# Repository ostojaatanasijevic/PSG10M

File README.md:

# PSG10M

PSG10M is a simple 10 MHz signal generator.

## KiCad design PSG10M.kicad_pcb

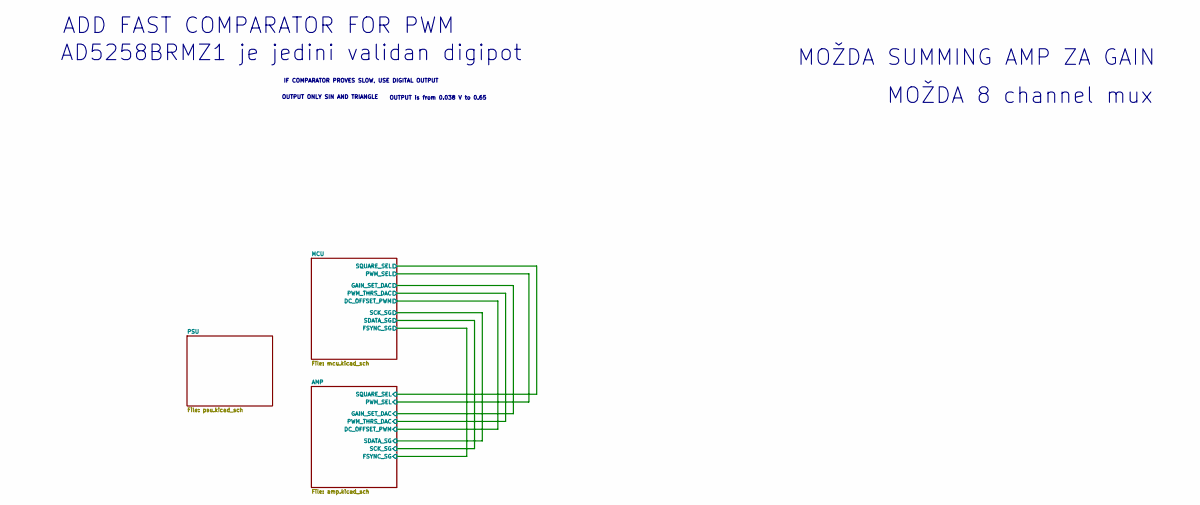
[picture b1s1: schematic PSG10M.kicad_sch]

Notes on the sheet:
OUTPUT is from 0.038 V to 0.65
IF COMPARATOR PROVES SLOW, USE DIGITAL OUTPUT
ADD FAST COMPARATOR FOR PWM
MOŽDA 8 channel mux
OUTPUT ONLY SIN AND TRIANGLE
AD5258BRMZ1 je jedini validan digipot
MOŽDA SUMMING AMP ZA GAIN

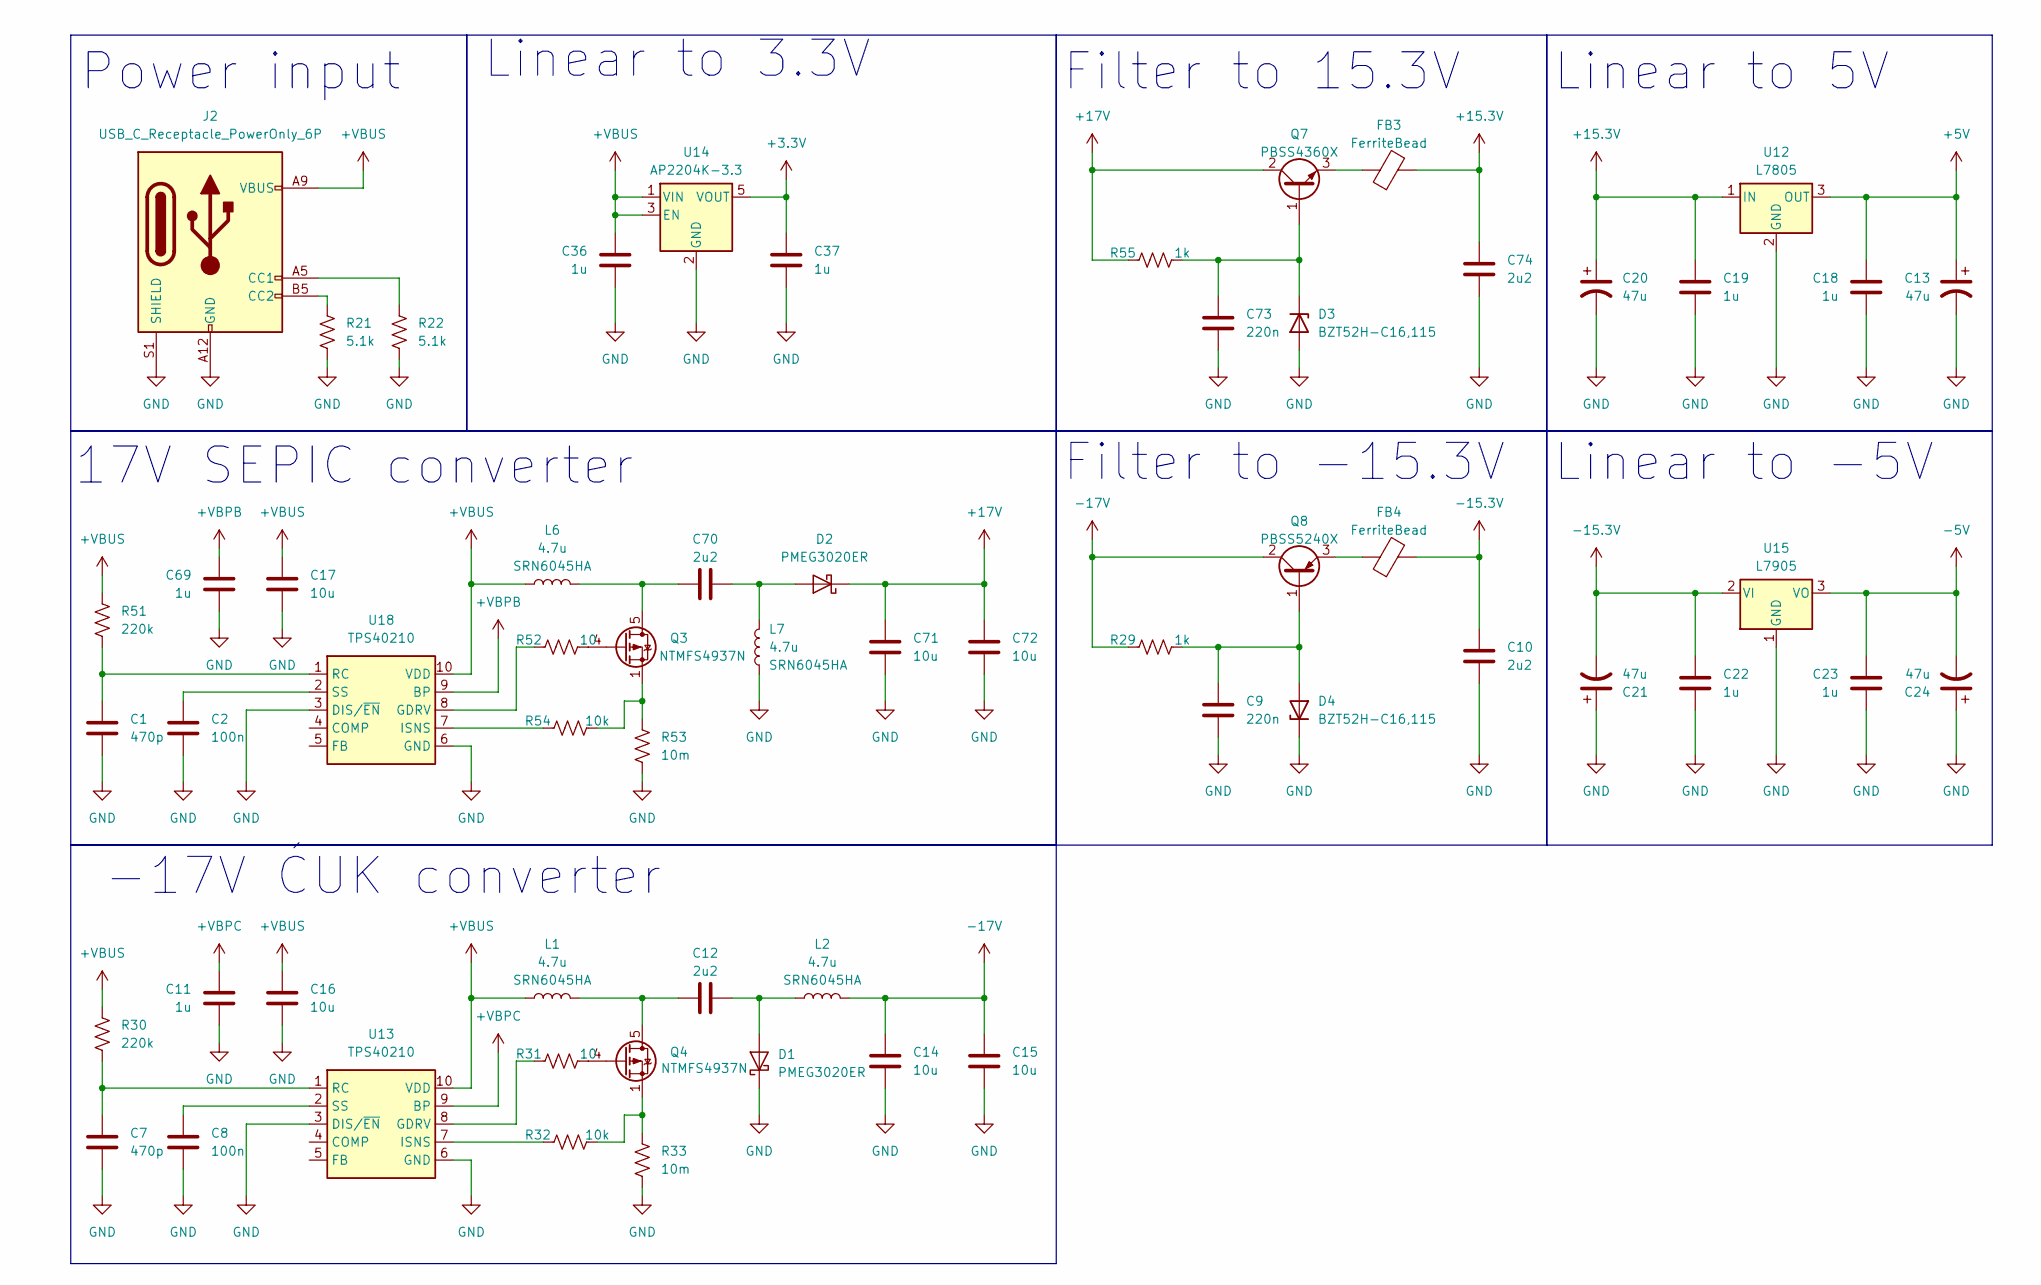
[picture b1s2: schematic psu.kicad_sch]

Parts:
C1, C7: 470p; R_0603_1608Metric_Pad0.98x0.95mm_HandSolder
C2, C8: 100n; R_0603_1608Metric_Pad0.98x0.95mm_HandSolder
C9, C73: 220n; R_0603_1608Metric_Pad0.98x0.95mm_HandSolder
C10, C12, C70, C74: 2u2; R_1206_3216Metric_Pad1.30x1.75mm_HandSolder
C11, C18, C19, C22, C23, C36, C37, C69: 1u; R_0603_1608Metric_Pad0.98x0.95mm_HandSolder
C13, C20, C21, C24: 47u; CP_Radial_D5.0mm_P2.00mm
C14, C15, C16, C17, C71, C72: 10u; R_1206_3216Metric
D1, D2: PMEG3020ER; D_SOD-128
D3, D4: BZT52H-C16,115; D_SOD-123F
FB3, FB4: FerriteBead
J2: USB_C_Receptacle_PowerOnly_6P; USB_C_Receptacle_GCT_USB4125-xx-x_6P_TopMnt_Horizontal
L1, L2, L6, L7: 4.7u; L_Bourns_SRN6045TA; Partname SRN6045HA
Q3, Q4: NTMFS4937N; PowerPAK_SO-8_Single
Q7: PBSS4360X; SOT-89-3
Q8: PBSS5240X; SOT-89-3
R21, R22: 5.1k; R_0603_1608Metric_Pad0.98x0.95mm_HandSolder
R29, R55: 1k; R_0603_1608Metric_Pad0.98x0.95mm_HandSolder
R30, R51: 220k; R_0603_1608Metric_Pad0.98x0.95mm_HandSolder
R31, R52: 10; R_0603_1608Metric_Pad0.98x0.95mm_HandSolder
R32, R54: 10k; R_0603_1608Metric_Pad0.98x0.95mm_HandSolder
R33, R53: 10m; R_2512_6332Metric_Pad1.40x3.35mm_HandSolder
U12: L7805; TO-220-3_Vertical
U13, U18: TPS40210; HVSSOP-10-1EP_3x3mm_P0.5mm_EP1.57x1.88mm
U14: AP2204K-3.3; SOT-23-5
U15: L7905; TO-220-3_Vertical

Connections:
+3.3V: C37.1, U14.5 (VOUT); also elsewhere on the board
+5V: C13.1, C18.1, U12.3 (OUT); also elsewhere on the board
+15.3V: C19.1, C20.1, C74.2, FB3.2, U12.1 (IN)
+17V: C71.1, C72.1, D2.1 (K), Q7.2 (C), R55.2
+VBPB: C69.1, U18.9 (BP)
+VBPC: C11.1, U13.9 (BP)
+VBUS: C16.1, C17.1, C36.1, J2.A9 (VBUS), J2.B9 (VBUS), L1.1, L6.1, R30.2, R51.2, U13.10 (VDD), U14.1 (VIN), U14.3 (EN), U18.10 (VDD); also elsewhere on the board
-5V: C23.1, C24.2, U15.3 (VO); also elsewhere on the board
-15.3V: C10.2, C21.2, C22.1, FB4.2, U15.2 (VI)
-17V: C14.1, C15.1, L2.2, Q8.2 (C), R29.2
GND: C1.2, C2.2, C7.2, C8.2, C9.2, C10.1, C11.2, C13.2, C14.2, C15.2, C16.2, C17.2, C18.2, C19.2, C20.2, C21.1, C22.2, C23.2, C24.1, C36.2, C37.2, C69.2, C71.2, C72.2, C73.2, C74.1, D1.1 (K), D3.2 (A), D4.1 (K), J2.A12 (GND), J2.B12 (GND), J2.S1 (SHIELD), L7.1, R21.1, R22.1, R33.2, R53.2, U12.2 (GND), U13.3 (DIS/~EN), U13.6 (GND), U14.2 (GND), U15.1 (GND), U18.3 (DIS/~EN), U18.6 (GND); also elsewhere on the board
unnamed: C12.2, D1.2 (A), L2.1
unnamed: C70.2, D2.2 (A), L7.2
unnamed: C73.1, D3.1 (K), Q7.1 (B), R55.1
unnamed: C9.1, D4.2 (A), Q8.1 (B), R29.1
unnamed: J2.A5 (CC1), R22.2
unnamed: J2.B5 (CC2), R21.2
unnamed: C70.1, L6.2, Q3.5 (D)
unnamed: Q3.4 (G), R52.1
unnamed: Q3.1 (S), Q3.2 (S), Q3.3 (S), R53.1, R54.1
unnamed: C12.1, L1.2, Q4.5 (D)
unnamed: Q4.4 (G), R31.1
unnamed: Q4.1 (S), Q4.2 (S), Q4.3 (S), R32.1, R33.1
unnamed: FB3.1, Q7.3 (E)
unnamed: FB4.1, Q8.3 (E)
unnamed: R31.2, U13.8 (GDRV)
unnamed: R32.2, U13.7 (ISNS)
unnamed: C7.1, R30.1, U13.1 (RC)
unnamed: C8.1, U13.2 (SS)
unnamed: R52.2, U18.8 (GDRV)
unnamed: R54.2, U18.7 (ISNS)
unnamed: C1.1, R51.1, U18.1 (RC)
unnamed: C2.1, U18.2 (SS)

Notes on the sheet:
Filter to 15.3V
Linear to 5V
Linear to -5V
-17V ĆUK converter
Filter to -15.3V
17V SEPIC converter
Power input
Linear to 3.3V

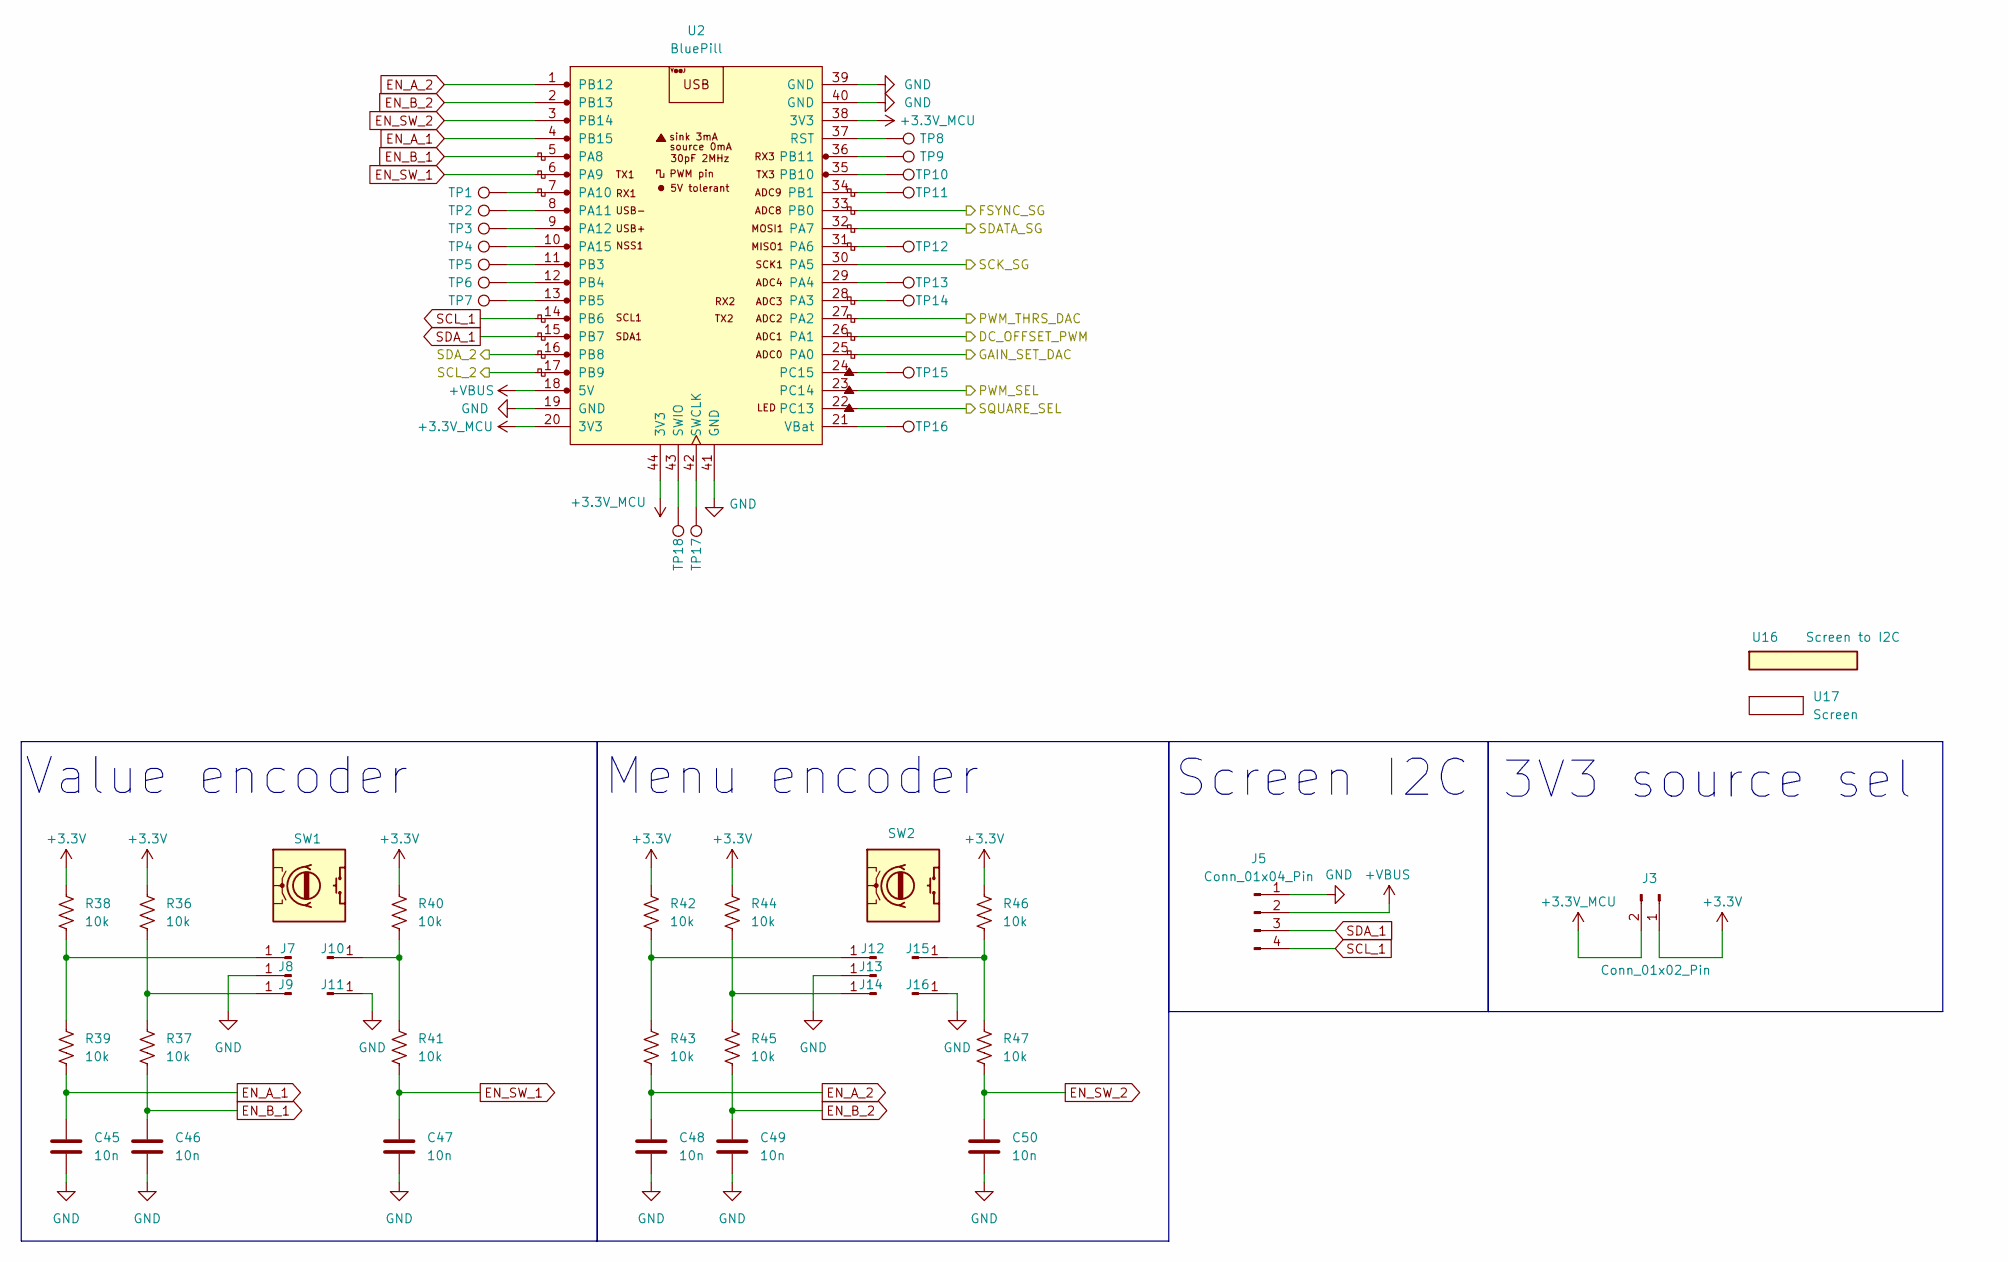
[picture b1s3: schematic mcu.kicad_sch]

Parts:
C45, C46, C47, C48, C49, C50: 10n; R_0603_1608Metric_Pad0.98x0.95mm_HandSolder
J3: Conn_01x02_Pin; PinHeader_1x02_P2.54mm_Vertical
J5: Conn_01x04_Pin; PinHeader_1x04_P2.54mm_Vertical
J7, J8, J9, J10, J11, J12, J13, J14, J15, J16: Conn_01x01_Pin; PinHeader_1x01_P2.54mm_Vertical
R36, R37, R38, R39, R40, R41, R42, R43, R44, R45, R46, R47: 10k; R_0603_1608Metric_Pad0.98x0.95mm_HandSolder
SW1, SW2: RotaryEncoder_Switch; RotaryEncoder_Bourns_Vertical_PEC12R-3x17F-Sxxxx
TP1, TP2, TP3, TP4, TP5, TP6, TP7, TP8, TP9, TP10, TP11, TP12, TP13, TP14, TP15, TP16, TP17, TP18: TestPoint; TestPoint_Pad_D3.0mm
U2: BluePill
U16: Screen to I2C; screen_to_i2c
U17: Screen; 2x16_vertical

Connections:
+3.3V: J3.1, R36.2, R38.2, R40.2, R42.2, R44.2, R46.2; also elsewhere on the board
+3.3V_MCU: J3.2, U2.20 (3V3), U2.38 (3V3), U2.44 (3V3)
+VBUS: J5.2, U2.18 (5V); also elsewhere on the board
/AMP/DC_OFFSET_PWM: U2.26 (PA1); also elsewhere on the board
/AMP/FSYNC_SG: U2.33 (PB0); also elsewhere on the board
/AMP/GAIN_SET_DAC: U2.25 (PA0); also elsewhere on the board
/AMP/PWM_SEL: U2.23 (PC14); also elsewhere on the board
/AMP/PWM_THRS_DAC: U2.27 (PA2); also elsewhere on the board
/AMP/SCK_SG: U2.32 (PA7); also elsewhere on the board
/AMP/SDATA_SG: U2.30 (PA5); also elsewhere on the board
/AMP/SQUARE_SEL: U2.22 (PC13); also elsewhere on the board
/MCU/SCL_2: U2.17 (PB9)
/MCU/SDA_2: U2.16 (PB8)
EN_A_1: C45.2, R39.1, U2.4 (PB15)
EN_A_2: C48.2, R43.1, U2.1 (PB12)
EN_B_1: C46.2, R37.1, U2.5 (PA8)
EN_B_2: C49.2, R45.1, U2.2 (PB13)
EN_SW_1: C47.2, R41.1, U2.6 (PA9)
EN_SW_2: C50.2, R47.1, U2.3 (PB14)
GND: C45.1, C46.1, C47.1, C48.1, C49.1, C50.1, J5.1, J8.1, J11.1, J13.1, J16.1, U2.19 (GND), U2.39 (GND), U2.40 (GND), U2.41 (GND); also elsewhere on the board
unnamed: J7.1, R38.1, R39.2
unnamed: J9.1, R36.1, R37.2
unnamed: J10.1, R40.1, R41.2
unnamed: J12.1, R42.1, R43.2
unnamed: J14.1, R44.1, R45.2
unnamed: J15.1, R46.1, R47.2
unnamed: TP14.1, U2.28 (PA3)
unnamed: TP13.1, U2.29 (PA4)
unnamed: TP12.1, U2.31 (PA6)
unnamed: TP1.1, U2.7 (PA10)
unnamed: TP2.1, U2.8 (PA11)
unnamed: TP3.1, U2.9 (PA12)
unnamed: TP4.1, U2.10 (PA15)
unnamed: TP11.1, U2.34 (PB1)
unnamed: TP5.1, U2.11 (PB3)
unnamed: TP6.1, U2.12 (PB4)
unnamed: TP7.1, U2.13 (PB5)
unnamed: TP10.1, U2.35 (PB10)
unnamed: TP9.1, U2.36 (PB11)
unnamed: TP15.1, U2.24 (PC15)
unnamed: TP8.1, U2.37 (RST)
unnamed: TP17.1, U2.42 (SWCLK)
unnamed: TP18.1, U2.43 (SWIO)
unnamed: TP16.1, U2.21 (VBat)
SCL_1: J5.4, U2.14 (PB6)
SDA_1: J5.3, U2.15 (PB7)

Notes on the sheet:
Screen I2C
Menu encoder
3V3 source sel
Value encoder

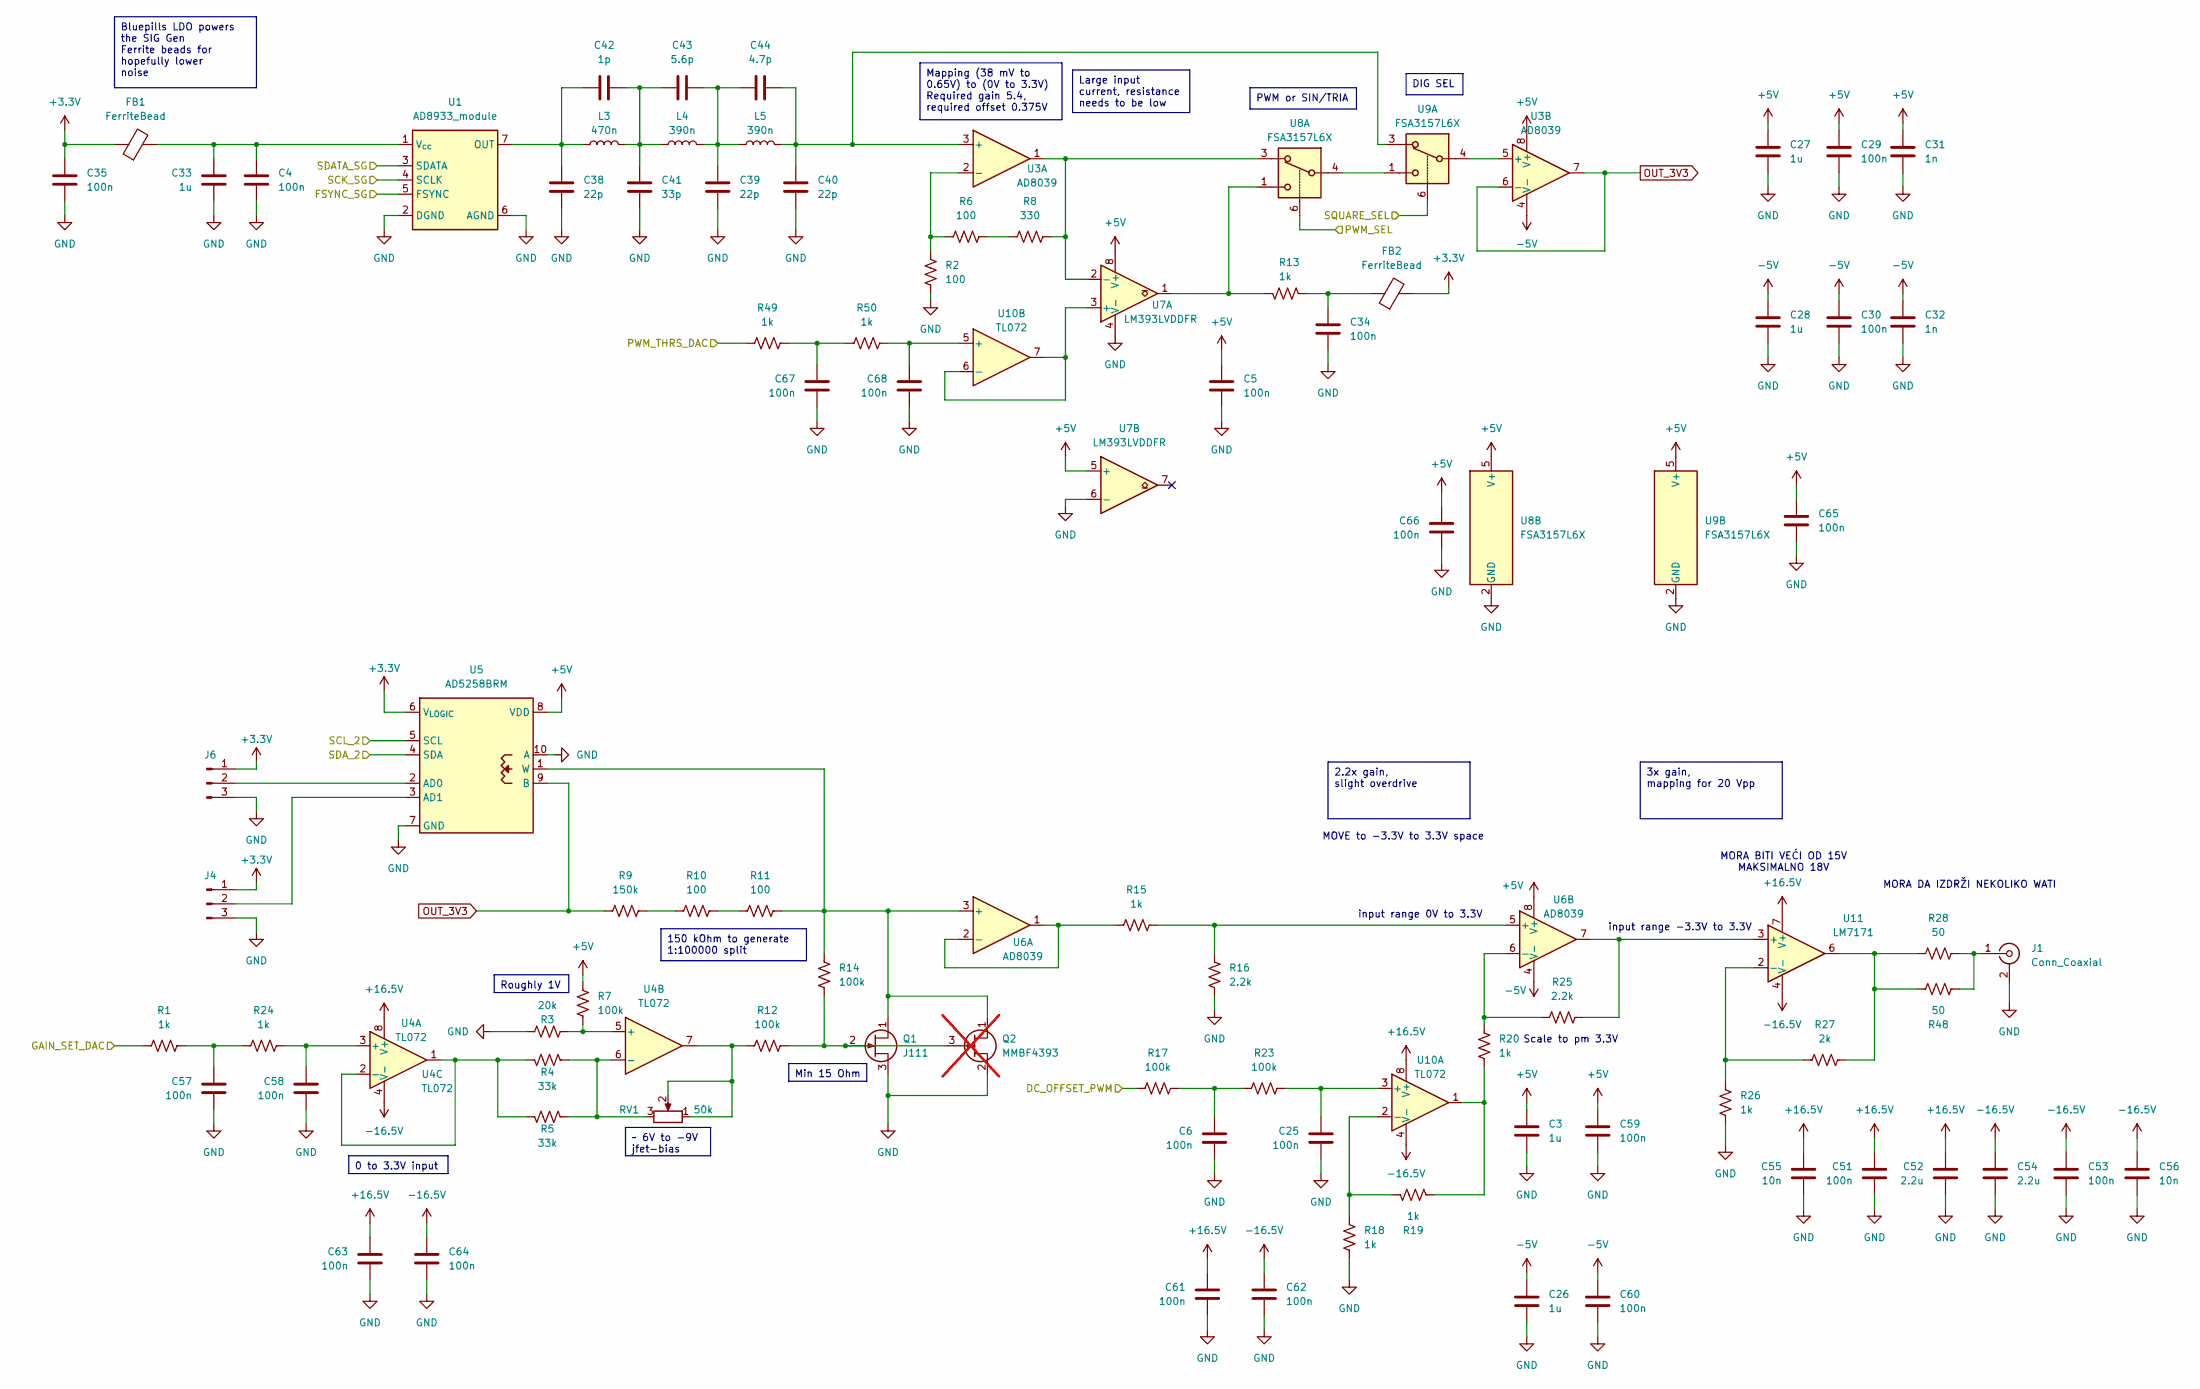
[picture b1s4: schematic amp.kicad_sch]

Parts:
C3, C26, C27, C28, C33: 1u; R_0603_1608Metric_Pad0.98x0.95mm_HandSolder
C4, C5, C6, C25, C34, C35, C51, C53, C57, C58, C61, C62, C63, C64, C65, C66, C67, C68: 100n; C_0603_1608Metric_Pad1.08x0.95mm_HandSolder
C29, C30, C59, C60: 100n; R_0603_1608Metric_Pad0.98x0.95mm_HandSolder
C31, C32: 1n; R_0603_1608Metric_Pad0.98x0.95mm_HandSolder
C38, C39, C40: 22p; C_0603_1608Metric_Pad1.08x0.95mm_HandSolder
C41: 33p; C_0603_1608Metric_Pad1.08x0.95mm_HandSolder
C42: 1p; C_0603_1608Metric_Pad1.08x0.95mm_HandSolder
C43: 5.6p; C_0603_1608Metric_Pad1.08x0.95mm_HandSolder
C44: 4.7p; C_0603_1608Metric_Pad1.08x0.95mm_HandSolder
C52, C54: 2.2u; C_1206_3216Metric_Pad1.33x1.80mm_HandSolder
C55, C56: 10n; C_0603_1608Metric_Pad1.08x0.95mm_HandSolder
FB1, FB2: FerriteBead; L_0603_1608Metric_Pad1.05x0.95mm_HandSolder
J1: Conn_Coaxial; BNC_Amphenol_B6252HB-NPP3G-50_Horizontal
J4, J6: Conn_01x03_Pin; PinHeader_1x03_P2.54mm_Vertical
L3: 470n; L_0603_1608Metric
L4, L5: 390n; L_0603_1608Metric
Q1: J111; TO-92_Inline_Wide
Q2: MMBF4393; SOT-23; not fitted
R1, R13, R15, R18, R19, R20, R24, R26, R49, R50: 1k; R_0603_1608Metric_Pad0.98x0.95mm_HandSolder
R2, R6, R10, R11: 100; R_0603_1608Metric_Pad0.98x0.95mm_HandSolder
R3: 20k; R_0603_1608Metric_Pad0.98x0.95mm_HandSolder
R4, R5: 33k; R_0603_1608Metric_Pad0.98x0.95mm_HandSolder
R7, R12, R14, R17, R23: 100k; R_0603_1608Metric_Pad0.98x0.95mm_HandSolder
R8: 330; R_0603_1608Metric_Pad0.98x0.95mm_HandSolder
R9: 150k; R_0603_1608Metric_Pad0.98x0.95mm_HandSolder
R16, R25: 2.2k; R_0603_1608Metric_Pad0.98x0.95mm_HandSolder
R27: 2k; R_0603_1608Metric_Pad0.98x0.95mm_HandSolder
R28, R48: 50; R_0603_1608Metric_Pad0.98x0.95mm_HandSolder
RV1: 50k; Potentiometer_Bourns_3296W_Vertical
U1: AD8933_module; AD9833_module
U3, U6: AD8039; SOIC-8_3.9x4.9mm_P1.27mm
U4, U10: TL072; SOIC-8_3.9x4.9mm_P1.27mm
U5: AD5258BRM; MSOP-10_3x3mm_P0.5mm
U7: LM393LVDDFR; SOT-223-8
U8, U9: FSA3157L6X; SOT-23-6_Handsoldering
U11: LM7171; SOIC-8_3.9x4.9mm_P1.27mm

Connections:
+3.3V: C35.1, FB1.1, FB2.2, J4.1, J6.1, U5.6 (V_{LOGIC}); also elsewhere on the board
+5V: C3.2, C5.1, C27.2, C29.2, C31.2, C59.2, C65.1, C66.1, R7.2, U3.8 (V+), U5.8 (VDD), U6.8 (V+), U7.5 (+), U7.8 (V+), U8.5 (V+), U9.5 (V+); also elsewhere on the board
+16.5V: C51.1, C52.1, C55.1, C61.1, C63.1, U4.8 (V+), U10.8 (V+), U11.7 (V+)
-5V: C26.2, C28.2, C30.2, C32.2, C60.2, U3.4 (V-), U6.4 (V-); also elsewhere on the board
-16.5V: C53.1, C54.1, C56.1, C62.1, C64.1, U4.4 (V-), U10.4 (V-), U11.4 (V-)
/AMP/DC_OFFSET_PWM: R17.1; also elsewhere on the board
/AMP/FSYNC_SG: U1.5 (FSYNC); also elsewhere on the board
/AMP/GAIN_SET_DAC: R1.1; also elsewhere on the board
/AMP/PWM_SEL: U8.6; also elsewhere on the board
/AMP/PWM_THRS_DAC: R49.1; also elsewhere on the board
/AMP/SCK_SG: U1.4 (SCLK); also elsewhere on the board
/AMP/SCL_2: U5.5 (SCL)
/AMP/SDATA_SG: U1.3 (SDATA); also elsewhere on the board
/AMP/SDA_2: U5.4 (SDA)
/AMP/SQUARE_SEL: U9.6; also elsewhere on the board
GND: C3.1, C4.2, C5.2, C6.2, C25.2, C26.1, C27.1, C28.1, C29.1, C30.1, C31.1, C32.1, C33.1, C34.2, C35.2, C38.2, C39.2, C40.2, C41.2, C51.2, C52.2, C53.2, C54.2, C55.2, C56.2, C57.2, C58.2, C59.1, C60.1, C61.2, C62.2, C63.2, C64.2, C65.2, C66.2, C67.2, C68.2, J1.2 (Ext), J4.3, J6.3, Q1.3 (S), Q2.2 (S), R2.1, R3.1, R16.1, R18.1, R26.1, U1.2 (DGND), U1.6 (AGND), U5.7 (GND), U5.10 (A), U7.4 (V-), U7.6 (-), U8.2 (GND), U9.2 (GND); also elsewhere on the board
unnamed: C6.1, R17.2, R23.1
unnamed: C34.1, FB2.1, R13.2
unnamed: C39.1, C43.2, C44.1, L4.2, L5.1
unnamed: C41.1, C42.2, C43.1, L3.2, L4.1
unnamed: C57.1, R1.2, R24.1
unnamed: C67.1, R49.2, R50.1
unnamed: J1.1 (In), R28.2, R48.1
unnamed: J4.2, U5.3 (AD1)
unnamed: J6.2, U5.2 (AD0)
unnamed: Q1.1 (D), Q2.1 (D), R11.2, R14.2, U5.1 (W), U6.3 (+)
unnamed: Q1.2 (G), Q2.3 (G), R12.1, R14.1
unnamed: R6.2, R8.1
unnamed: R9.2, R10.1
unnamed: R10.2, R11.1
unnamed: R12.2, RV1.1, RV1.2, U4.7
unnamed: R13.1, U7.1, U8.1
unnamed: R19.2, R20.1, U10.1
unnamed: R27.2, R28.1, R48.2, U11.6
unnamed: C38.1, C42.1, L3.1, U1.7 (OUT)
unnamed: C4.1, C33.2, FB1.2, U1.1 (V_{cc})
unnamed: C40.1, C44.2, L5.2, U3.3 (+), U9.3
unnamed: R2.2, R6.1, U3.2 (-)
unnamed: U3.5 (+), U9.4
unnamed: C58.1, R24.2, U4.3 (+)
unnamed: R4.1, R5.1, U4.1, U4.2 (-)
unnamed: R3.2, R7.1, U4.5 (+)
unnamed: R4.2, R5.2, RV1.3, U4.6 (-)
unnamed: R15.1, U6.1, U6.2 (-)
unnamed: R15.2, R16.2, U6.5 (+)
unnamed: R20.2, R25.1, U6.6 (-)
unnamed: R8.2, U3.1, U7.2 (-), U8.3
unnamed: U8.4, U9.1
unnamed: C25.1, R23.2, U10.3 (+)
unnamed: R18.2, R19.1, U10.2 (-)
unnamed: C68.1, R50.2, U10.5 (+)
unnamed: U7.3 (+), U10.6 (-), U10.7
unnamed: R25.2, U6.7, U11.3 (+)
unnamed: R26.2, R27.1, U11.2 (-)
OUT_3V3: R9.1, U3.6 (-), U3.7, U5.9 (B)

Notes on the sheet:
~ 6V to -9V jfet-bias
150 kOhm to generate 1:100000 split
Roughly 1V
0 to 3.3V input
DIG SEL
Mapping (38 mV to 0.65V) to (0V to 3.3V) Required gain 5.4, required offset 0.375V
PWM or SIN/TRIA
2.2x gain, slight overdrive
Large input current, resistance needs to be low
3x gain, mapping for 20 Vpp
Min 15 Ohm
Bluepills LDO powers the SIG Gen Ferrite beads for hopefully lower noise
MORA BITI VEĆI OD 15V MAKSIMALNO 18V
Scale to pm 3.3V
MORA DA IZDRŽI NEKOLIKO WATI
MOVE to -3.3V to 3.3V space
input range -3.3V to 3.3V
input range 0V to 3.3V

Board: 2 copper layers, 201 parts (2 on the bottom side), 113 nets, no tracks yet.

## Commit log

2024-10-16 Init
2024-10-16 Ide nekako idk.
2024-10-27 JFET-added
2024-10-27 Added DC offset, specifics TBD
2024-10-27 Save game. Power supply next.
2024-10-27 Working on PSY. Oddball values are fun.
2024-11-01 Update.
2024-11-02 Progress.
2024-11-02 Savegame.
2024-11-02 Added readme.
2024-11-02 Img.
2024-11-02 Lkkn.
2024-11-03 Updated spec.
2024-12-12 Add the tested push-pull rail generator.
2025-01-06 SEPIC and CUK
